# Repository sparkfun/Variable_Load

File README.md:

SparkFun Variable Load
==========================================

[*Variable Load (KIT-14449)*](https://www.sparkfun.com/products/14449)

The Variable Load is a digitally controllable load for testing power supplies.
It can test up to 30V at 4A, with a limit of 15W.

Repository Contents
-------------------
* **/Hardware** - All Eagle design files (.brd, .sch)
* **/Firmware** - Firmware files for this project.
* **/Production** - Test bed files and production panel files

Documentation
--------------

* **[Hookup Guide - Revised](https://learn.sparkfun.com/tutorials/variable-load-hookup-guide---revised)** - Latest basic hookup guide for the Variable Load.
* ***[Hookup Guide (RETIRED)](https://learn.sparkfun.com/tutorials/variable-load-hookup-guide)** - Basic hookup guide for the Variable Load for boards purchased purchased prior to 24 May 2018.*

License Information
-------------------

This product is _**open source**_! 

Please review the LICENSE.md file for license information. 

If you have any questions or concerns on licensing, please contact techsupport@sparkfun.com.

Distributed as-is; no warranty is given.

- Your friends at SparkFun.

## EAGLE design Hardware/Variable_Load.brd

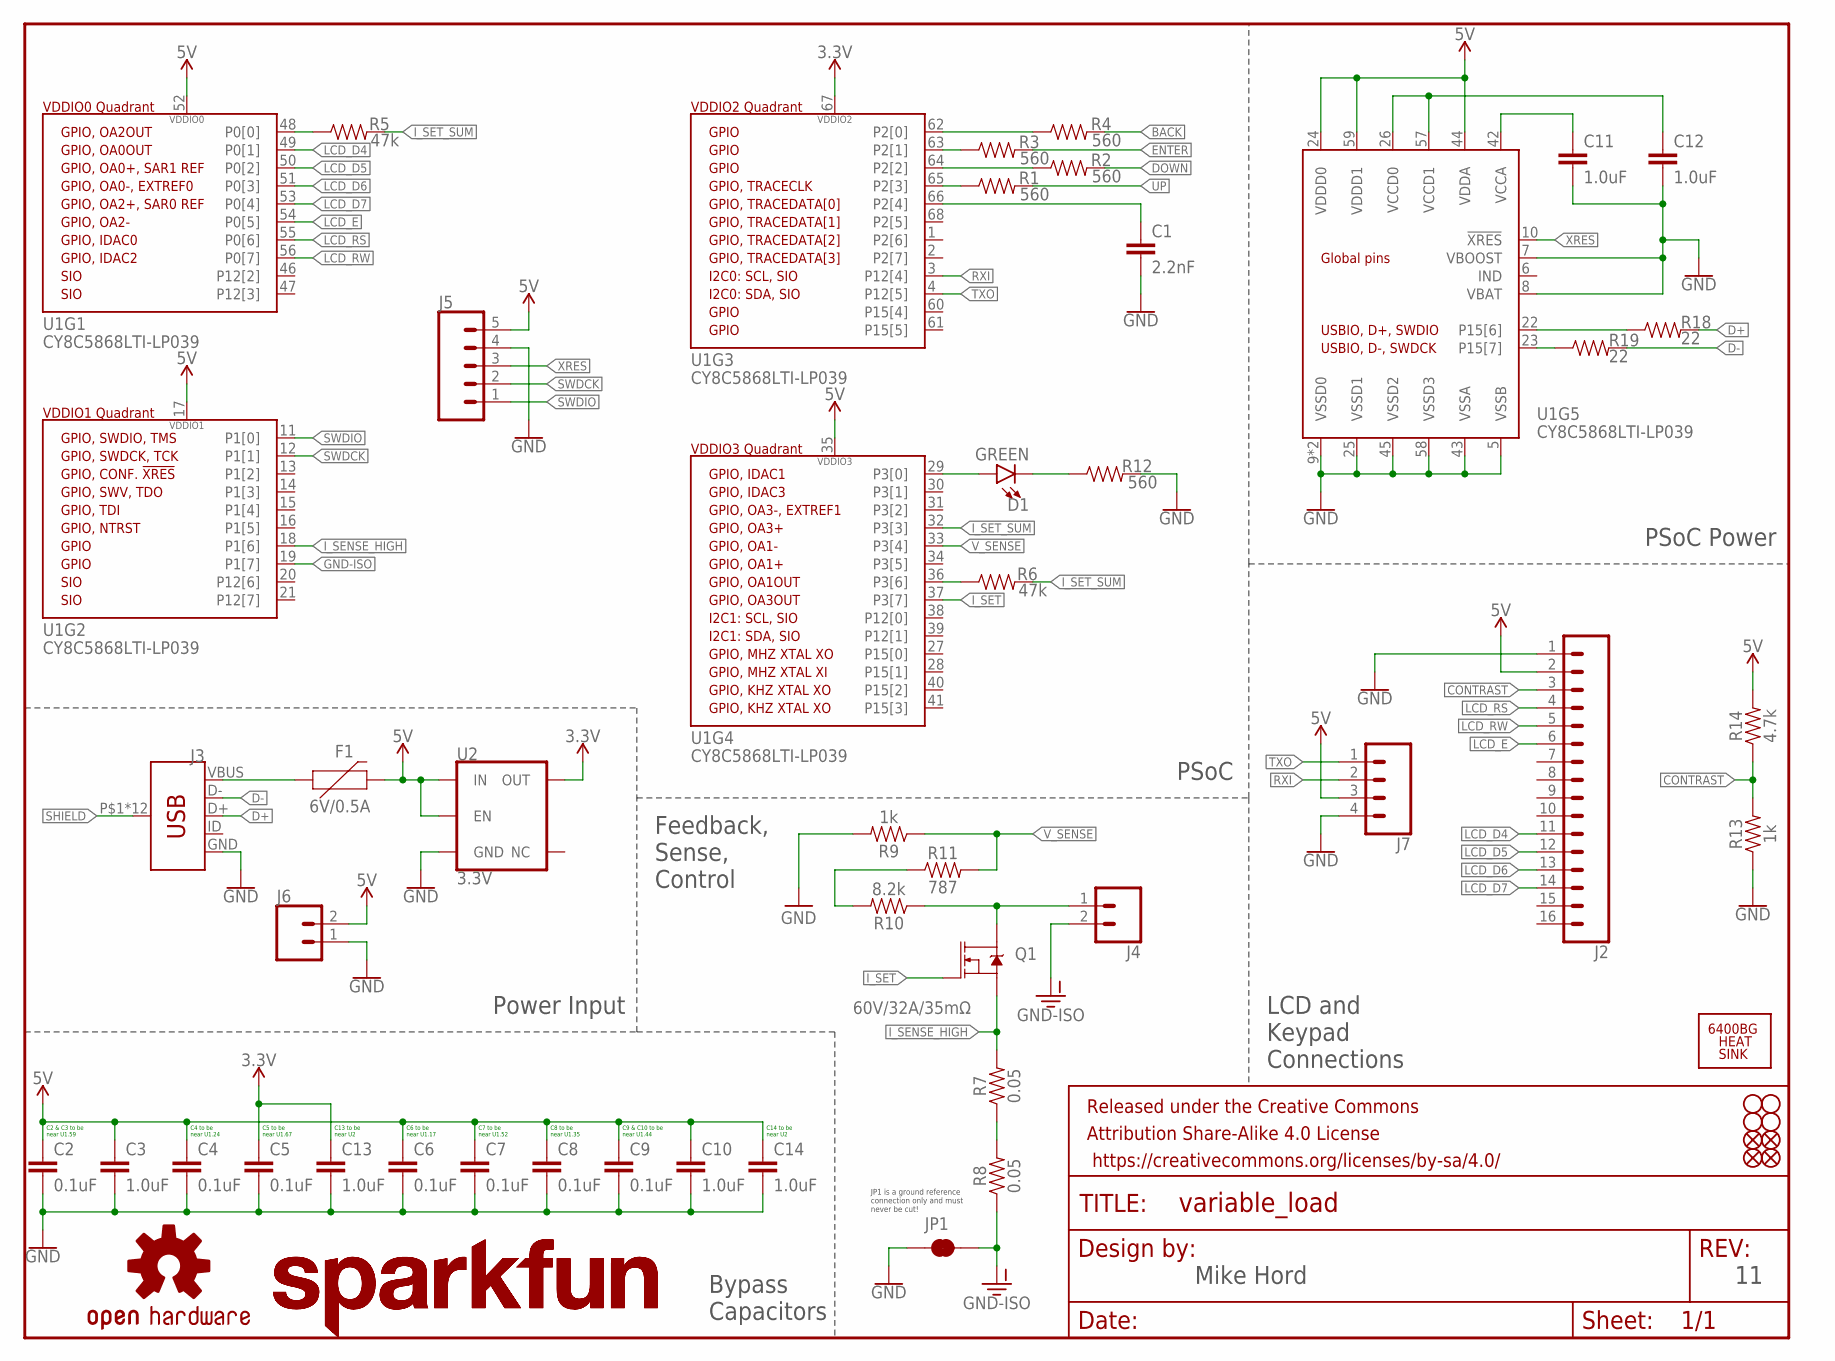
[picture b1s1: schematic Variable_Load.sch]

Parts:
C1: 2.2nF; 0603
C2, C4, C5, C6, C7, C8, C9: 0.1uF; 0402
C3, C10, C11, C12, C13, C14: 1.0uF; 0402
D1: GREEN; LED-1206-BOTTOM
F1: 6V/0.5A; 1206
FD1, FD2, FD3, FD4: FIDUCIAL1X2; FIDUCIAL-1X2
FRAME1: FRAME-LETTER; CREATIVE_COMMONS
H1: 6400BG_HEATSINK
H2, H3, H4, H5: STAND-OFF
J2: CONN_16; 1X16
J3: AMP FCI 10103594-0001LF; USB-MICROB-PTH
J4: CONN_023.5MM_LOCK; SCREWTERMINAL-3.5MM-2_LOCK
J5: CONN_05; 1X05
J6: CONN_02; 1X02
J7: CONN_04; 1X04
JP1: JUMPER-SMT_2_NC_TRACE_NO-SILK; SMT-JUMPER_2_NC_TRACE_NO-SILK
LOGO1: OSHW-LOGOM; OSHW-LOGO-M
LOGO2, LOGO3: SFE_LOGO_NAME.3_INCH; SFE_LOGO_NAME_.3
Q1: 60V/32A/35mΩ; TO220V
R1, R2, R3, R4, R12: 560; 0402
R5, R6: 47k; 0603
R7, R8: 0.05; 2512
R9, R13: 1k; 0603
R10: 8.2k; 0603
R11: 787; 0603
R14: 4.7k; 0603
R18, R19: 22; 0402-RES
U1: CY8C5868LTI-LP039; QFN-68
U2: 3.3V; SOT23-5

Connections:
3.3V: C5.1, C13.1, U1.67 (VDDIO2), U2.5 (OUT)
5V: C2.1, C3.1, C4.1, C6.1, C7.1, C8.1, C9.1, C10.1, C14.1, F1.2, J2.2, J5.5, J6.2, J7.3, R14.2, U1.17 (VDDIO1), U1.24 (VDDD0), U1.35 (VDDIO3), U1.44 (VDDA), U1.52 (VDDIO0), U1.59 (VDDD1), U2.1 (IN), U2.3 (EN)
BACK: R4.2
CONTRAST: J2.3, R13.2, R14.1
D+: J3.D+, R18.2
D-: J3.D-, R19.2
DOWN: R2.2
ENTER: R3.2
GND: C1.2, C2.2, C3.2, C4.2, C5.2, C6.2, C7.2, C8.2, C9.2, C10.2, C11.2, C12.2, C13.2, C14.2, J2.1, J3.GND, J5.4, J6.1, J7.4, JP1.1, R9.2, R12.2, R13.1, U1.5 (VSSB), U1.7 (VBOOST), U1.8 (VBAT), U1.9 (VSSD0), U1.25 (VSSD1), U1.43 (VSSA), U1.45 (VSSD2), U1.58 (VSSD3), U1.69 (VSSD0), U2.2 (GND)
GND-ISO: J4.2, JP1.2, R8.P$1 (1), U1.19 (P1[7])
I_SENSE_HIGH: Q1.3 (S), R7.P$2 (2), U1.18 (P1[6])
I_SET: Q1.1 (G), U1.37 (P3[7])
I_SET_SUM: R5.2, R6.2, U1.32 (P3[3])
LCD_D4: J2.11, U1.49 (P0[1])
LCD_D5: J2.12, U1.50 (P0[2])
LCD_D6: J2.13, U1.51 (P0[3])
LCD_D7: J2.14, U1.53 (P0[4])
LCD_E: J2.6, U1.54 (P0[5])
LCD_RS: J2.4, U1.55 (P0[6])
LCD_RW: J2.5, U1.56 (P0[7])
unnamed: R1.1, U1.65 (P2[3])
unnamed: R2.1, U1.64 (P2[2])
unnamed: R3.1, U1.63 (P2[1])
unnamed: R4.1, U1.62 (P2[0])
unnamed: C1.1, U1.66 (P2[4])
unnamed: C12.1, U1.26 (VCCD0), U1.57 (VCCD1)
unnamed: C11.1, U1.42 (VCCA)
unnamed: R18.1, U1.22 (P15[6])
unnamed: R19.1, U1.23 (P15[7])
unnamed: R5.1, U1.48 (P0[0])
unnamed: R6.1, U1.36 (P3[6])
unnamed: D1.A, U1.29 (P3[0])
unnamed: D1.C, R12.1
unnamed: F1.1, J3.VBUS
unnamed: J4.1, Q1.2 (D), R10.1
unnamed: R10.2, R11.1
unnamed: R7.P$1 (1), R8.P$2 (2)
RXI: J7.2, U1.3 (P12[4])
SHIELD: J3.P$1 (SHIELD), J3.P$2 (SHIELD), J3.P$3 (SHIELD), J3.P$4 (SHIELD), J3.P$6 (SHIELD), J3.P$8 (SHIELD), J3.P$10 (SHIELD), J3.P$12 (SHIELD), J3.SHEILD2 (SHIELD), J3.SHIELD, J3.SHIELD3 (SHIELD), J3.SHIELD4 (SHIELD)
SWDCK: J5.2, U1.12 (P1[1])
SWDIO: J5.1, U1.11 (P1[0])
TXO: J7.1, U1.4 (P12[5])
UP: R1.2
V_SENSE: R9.1, R11.2, U1.33 (P3[4])
XRES: J5.3, U1.10 (!XRES)

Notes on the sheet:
C2 & C3 to be near U1.59
C4 to be near U1.24
C5 to be near U1.67
C6 to be near U1.17
C7 to be near U1.52
C8 to be near U1.35
C9 & C10 to be near U1.44
C13 to be near U2
C14 to be near U2
Feedback, Sense, Control
Power Input
LCD and Keypad Connections
PSoC Power
PSoC
Bypass Capacitors
Mike Hord
JP1 is a ground reference connection only and must never be cut!

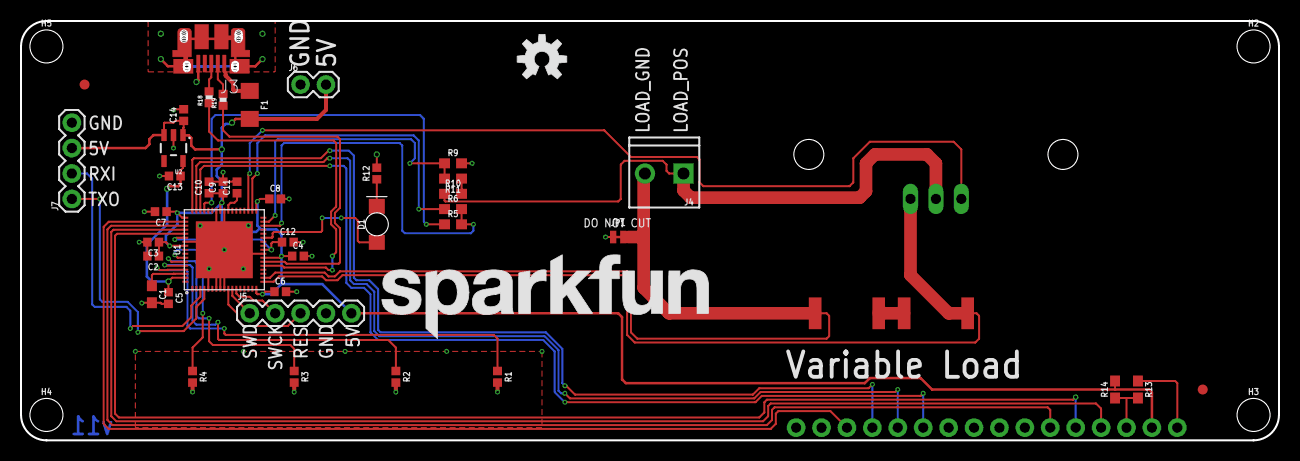
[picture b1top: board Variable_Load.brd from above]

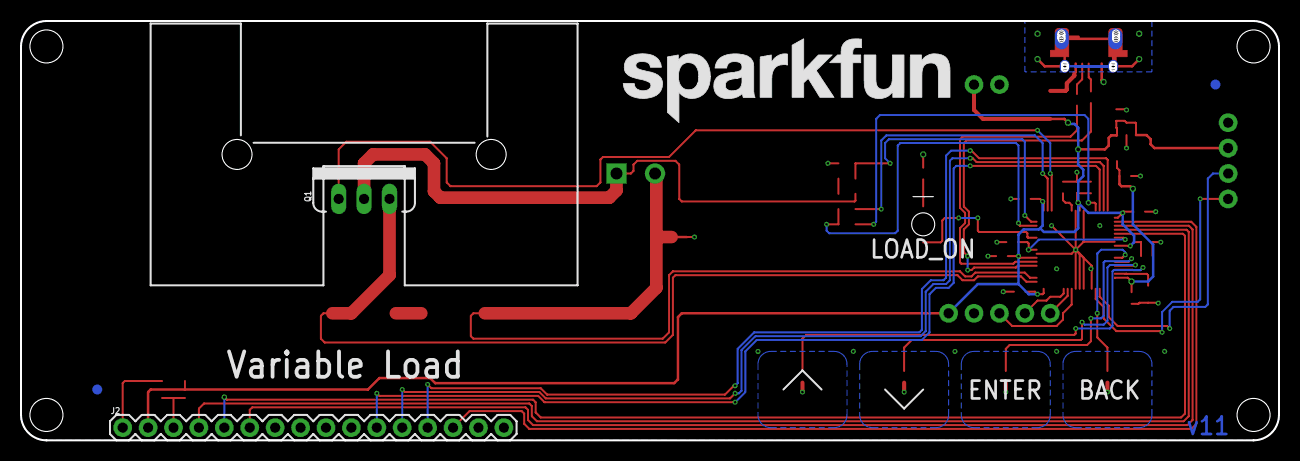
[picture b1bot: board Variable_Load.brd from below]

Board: 2 copper layers, 125.7 x 41.9 mm, 55 parts (6 on the bottom side), 41 nets.

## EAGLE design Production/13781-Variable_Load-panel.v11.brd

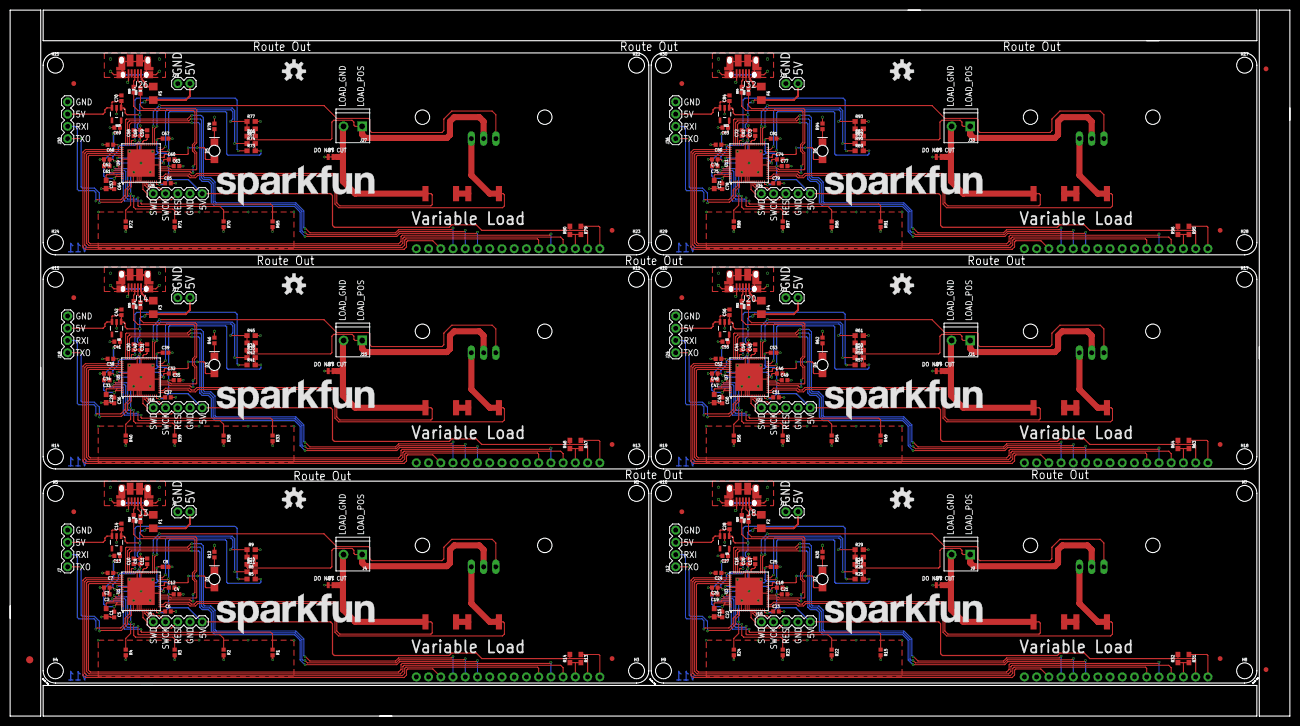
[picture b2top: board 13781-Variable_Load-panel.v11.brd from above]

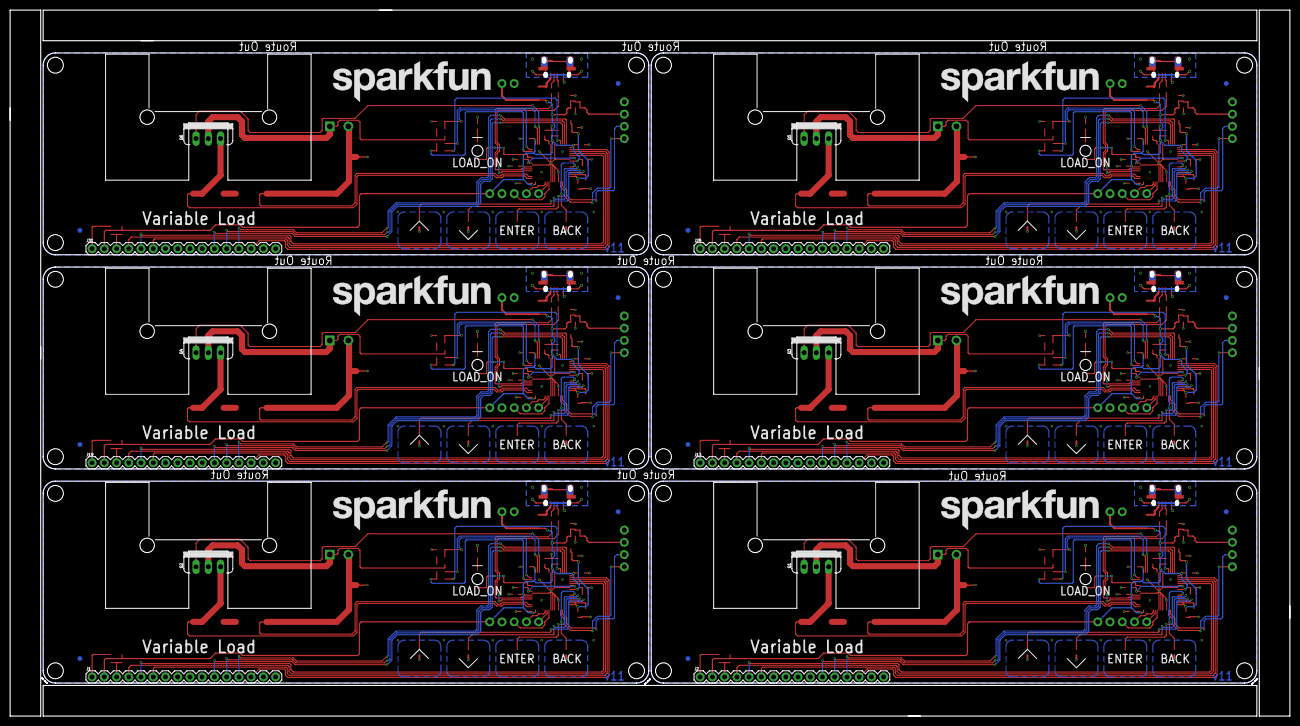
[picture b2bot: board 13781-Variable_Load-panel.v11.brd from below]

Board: 2 copper layers, 265.7 x 146.6 mm, 327 parts (36 on the bottom side), 246 nets.

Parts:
C1, C15, C29, C43, C57, C71: 2.2nF; 0603
C2, C4, C5, C6, C7, C8, C9, C19, C21, C22, C23, C24, C25, C26, C33, C35, C36, C37, C38, C39, C40, C47, C49, C50, C51, C52, C53, C54, C61, C63, C64, C65, C66, C67, C68, C75, C77, C78, C79, C80, C81, C82: 0.1uF; 0402
C3, C10, C11, C12, C13, C14, C16, C17, C18, C20, C27, C28, C30, C31, C32, C34, C41, C42, C44, C45, C46, C48, C55, C56, C58, C59, C60, C62, C69, C70, C72, C73, C74, C76, C83, C84: 1.0uF; 0402
D1, D2, D3, D4, D5, D6: GREEN; LED-1206-BOTTOM
E$1: FIDUCIAL-1.5X3
E$7, E$8: FIDUCIAL-1X2
F1, F2, F3, F4, F5, F6: 6V/0.5A; 1206
FD1, FD2, FD3, FD4, FD5, FD6, FD7, FD8, FD9, FD10, FD11, FD12, FD13, FD14, FD15, FD16, FD17, FD18, FD19, FD20, FD21, FD22, FD23, FD24: FIDUCIAL1X2; FIDUCIAL-1X2
H1, H6, H11, H16, H21, H26: 6400BG_HEATSINK
H2, H3, H4, H5, H7, H8, H9, H10, H12, H13, H14, H15, H17, H18, H19, H20, H22, H23, H24, H25, H27, H28, H29, H30: STAND-OFF
J1, J2, J13, J19, J25, J31: 1X16
J3, J8, J14, J20, J26, J32: AMP FCI 10103594-0001LF; USB-MICROB-PTH
J4, J9, J15, J21, J27, J33: SCREWTERMINAL-3.5MM-2_LOCK
J5, J10, J16, J22, J28, J34: 1X05
J6, J11, J17, J23, J29, J35: 1X02
J7, J12, J18, J24, J30, J36: 1X04
JP1, JP2, JP3, JP4, JP5, JP6: JUMPER-SMT_2_NC_TRACE_NO-SILK; SMT-JUMPER_2_NC_TRACE_NO-SILK
LOGO1, LOGO4, LOGO7, LOGO10, LOGO13, LOGO16: OSHW-LOGOM; OSHW-LOGO-M
LOGO2, LOGO3, LOGO5, LOGO6, LOGO8, LOGO9, LOGO11, LOGO12, LOGO14, LOGO15, LOGO17, LOGO18: SFE_LOGO_NAME.3_INCH; SFE_LOGO_NAME_.3
Q1, Q2, Q3, Q4, Q5, Q6: 60V/32A/35mΩ; TO220V
R1, R2, R3, R4, R12, R15, R22, R23, R24, R30, R33, R38, R39, R40, R46, R49, R54, R55, R56, R62, R65, R70, R71, R72, R78, R81, R86, R87, R88, R94: 560; 0402
R5, R6, R25, R26, R41, R42, R57, R58, R73, R74, R89, R90: 47k; 0603
R7, R8, R27, R28, R43, R44, R59, R60, R75, R76, R91, R92: 0.05; 2512
R9, R13, R29, R31, R45, R47, R61, R63, R77, R79, R93, R95: 1k; 0603
R10, R16, R34, R50, R66, R82: 8.2k; 0603
R11, R17, R35, R51, R67, R83: 787; 0603
R14, R32, R48, R64, R80, R96: 4.7k; 0603
R18, R19, R20, R21, R36, R37, R52, R53, R68, R69, R84, R85: 22; 0402-RES
U1, U3, U5, U7, U9, U11: CY8C5868LTI-LP039; QFN-68
U2, U4, U6, U8, U10, U12: 3.3V; SOT23-5

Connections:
3.3V: C5.1, C13.1, U1.67, U2.5
3.3V1: C22.1, C27.1, U3.67, U4.5
3.3V2: C36.1, C41.1, U5.67, U6.5
3.3V3: C50.1, C55.1, U7.67, U8.5
3.3V4: C64.1, C69.1, U9.67, U10.5
3.3V5: C78.1, C83.1, U11.67, U12.5
5V: C2.1, C3.1, C4.1, C6.1, C7.1, C8.1, C9.1, C10.1, C14.1, F1.2, J2.2, J5.5, J6.2, J7.3, R14.2, U1.17, U1.24, U1.35, U1.44, U1.52, U1.59, U2.1, U2.3
5V1: C16.1, C19.1, C20.1, C21.1, C23.1, C24.1, C25.1, C26.1, C28.1, F2.2, J1.2, J10.5, J11.2, J12.3, R32.2, U3.17, U3.24, U3.35, U3.44, U3.52, U3.59, U4.1, U4.3
5V2: C30.1, C33.1, C34.1, C35.1, C37.1, C38.1, C39.1, C40.1, C42.1, F3.2, J13.2, J16.5, J17.2, J18.3, R48.2, U5.17, U5.24, U5.35, U5.44, U5.52, U5.59, U6.1, U6.3
5V3: C44.1, C47.1, C48.1, C49.1, C51.1, C52.1, C53.1, C54.1, C56.1, F4.2, J19.2, J22.5, J23.2, J24.3, R64.2, U7.17, U7.24, U7.35, U7.44, U7.52, U7.59, U8.1, U8.3
5V4: C58.1, C61.1, C62.1, C63.1, C65.1, C66.1, C67.1, C68.1, C70.1, F5.2, J25.2, J28.5, J29.2, J30.3, R80.2, U9.17, U9.24, U9.35, U9.44, U9.52, U9.59, U10.1, U10.3
5V5: C72.1, C75.1, C76.1, C77.1, C79.1, C80.1, C81.1, C82.1, C84.1, F6.2, J31.2, J34.5, J35.2, J36.3, R96.2, U11.17, U11.24, U11.35, U11.44, U11.52, U11.59, U12.1, U12.3
CONTRAST: J2.3, R13.2, R14.1
CONTRAST1: J1.3, R31.2, R32.1
CONTRAST2: J13.3, R47.2, R48.1
CONTRAST3: J19.3, R63.2, R64.1
CONTRAST4: J25.3, R79.2, R80.1
CONTRAST5: J31.3, R95.2, R96.1
D+: J3.D+, R18.2
D+1: J8.D+, R20.2
D+2: J14.D+, R36.2
D+3: J20.D+, R52.2
D+4: J26.D+, R68.2
D+5: J32.D+, R84.2
D-: J3.D-, R19.2
D-1: J8.D-, R21.2
D-2: J14.D-, R37.2
D-3: J20.D-, R53.2
D-4: J26.D-, R69.2
D-5: J32.D-, R85.2
GND: C1.2, C2.2, C3.2, C4.2, C5.2, C6.2, C7.2, C8.2, C9.2, C10.2, C11.2, C12.2, C13.2, C14.2, J2.1, J3.GND, J5.4, J6.1, J7.4, JP1.1, R9.2, R12.2, R13.1, U1.5, U1.7, U1.8, U1.9, U1.25, U1.43, U1.45, U1.58, U1.69, U2.2
GND1: C15.2, C16.2, C17.2, C18.2, C19.2, C20.2, C21.2, C22.2, C23.2, C24.2, C25.2, C26.2, C27.2, C28.2, J1.1, J8.GND, J10.4, J11.1, J12.4, JP2.1, R29.2, R30.2, R31.1, U3.5, U3.7, U3.8, U3.9, U3.25, U3.43, U3.45, U3.58, U3.69, U4.2
GND2: C29.2, C30.2, C31.2, C32.2, C33.2, C34.2, C35.2, C36.2, C37.2, C38.2, C39.2, C40.2, C41.2, C42.2, J13.1, J14.GND, J16.4, J17.1, J18.4, JP3.1, R45.2, R46.2, R47.1, U5.5, U5.7, U5.8, U5.9, U5.25, U5.43, U5.45, U5.58, U5.69, U6.2
GND3: C43.2, C44.2, C45.2, C46.2, C47.2, C48.2, C49.2, C50.2, C51.2, C52.2, C53.2, C54.2, C55.2, C56.2, J19.1, J20.GND, J22.4, J23.1, J24.4, JP4.1, R61.2, R62.2, R63.1, U7.5, U7.7, U7.8, U7.9, U7.25, U7.43, U7.45, U7.58, U7.69, U8.2
GND4: C57.2, C58.2, C59.2, C60.2, C61.2, C62.2, C63.2, C64.2, C65.2, C66.2, C67.2, C68.2, C69.2, C70.2, J25.1, J26.GND, J28.4, J29.1, J30.4, JP5.1, R77.2, R78.2, R79.1, U9.5, U9.7, U9.8, U9.9, U9.25, U9.43, U9.45, U9.58, U9.69, U10.2
GND5: C71.2, C72.2, C73.2, C74.2, C75.2, C76.2, C77.2, C78.2, C79.2, C80.2, C81.2, C82.2, C83.2, C84.2, J31.1, J32.GND, J34.4, J35.1, J36.4, JP6.1, R93.2, R94.2, R95.1, U11.5, U11.7, U11.8, U11.9, U11.25, U11.43, U11.45, U11.58, U11.69, U12.2
GND-ISO: J4.2, JP1.2, R8.P$1, U1.19
GND-ISO1: J9.2, JP2.2, R28.P$1, U3.19
GND-ISO2: J15.2, JP3.2, R44.P$1, U5.19
GND-ISO3: J21.2, JP4.2, R60.P$1, U7.19
GND-ISO4: J27.2, JP5.2, R76.P$1, U9.19
GND-ISO5: J33.2, JP6.2, R92.P$1, U11.19
I_SENSE_HIGH: Q1.3, R7.P$2, U1.18
I_SENSE_HIGH1: Q2.3, R27.P$2, U3.18
I_SENSE_HIGH2: Q3.3, R43.P$2, U5.18
I_SENSE_HIGH3: Q4.3, R59.P$2, U7.18
I_SENSE_HIGH4: Q5.3, R75.P$2, U9.18
I_SENSE_HIGH5: Q6.3, R91.P$2, U11.18
I_SET: Q1.1, U1.37
I_SET1: Q2.1, U3.37
I_SET2: Q3.1, U5.37
I_SET3: Q4.1, U7.37
I_SET4: Q5.1, U9.37
I_SET5: Q6.1, U11.37
I_SET_SUM: R5.2, R6.2, U1.32
I_SET_SUM1: R25.2, R26.2, U3.32
I_SET_SUM2: R41.2, R42.2, U5.32
I_SET_SUM3: R57.2, R58.2, U7.32
I_SET_SUM4: R73.2, R74.2, U9.32
I_SET_SUM5: R89.2, R90.2, U11.32
LCD_D1: J1.11, U3.49
LCD_D2: J1.12, U3.50
LCD_D3: J1.13, U3.51
LCD_D4: J2.11, U1.49
LCD_D5: J2.12, U1.50
LCD_D6: J2.13, U1.51
LCD_D7: J2.14, U1.53
LCD_D8: J1.14, U3.53
LCD_D9: J13.11, U5.49
LCD_D10: J13.12, U5.50
LCD_D11: J13.13, U5.51
LCD_D12: J13.14, U5.53
LCD_D13: J19.11, U7.49
LCD_D14: J19.12, U7.50
LCD_D15: J19.13, U7.51
LCD_D16: J19.14, U7.53
LCD_D17: J25.11, U9.49
LCD_D18: J25.12, U9.50
LCD_D19: J25.13, U9.51
LCD_D20: J25.14, U9.53
LCD_D21: J31.11, U11.49
LCD_D22: J31.12, U11.50
LCD_D23: J31.13, U11.51
LCD_D24: J31.14, U11.53
LCD_E: J2.6, U1.54
LCD_E1: J1.6, U3.54
LCD_E2: J13.6, U5.54
LCD_E3: J19.6, U7.54
LCD_E4: J25.6, U9.54
LCD_E5: J31.6, U11.54
LCD_RS: J2.4, U1.55
LCD_RS1: J1.4, U3.55
LCD_RS2: J13.4, U5.55
LCD_RS3: J19.4, U7.55
LCD_RS4: J25.4, U9.55
LCD_RS5: J31.4, U11.55
LCD_RW: J2.5, U1.56
LCD_RW1: J1.5, U3.56
LCD_RW2: J13.5, U5.56
LCD_RW3: J19.5, U7.56
LCD_RW4: J25.5, U9.56
LCD_RW5: J31.5, U11.56
unnamed: R1.1, U1.65
unnamed: R2.1, U1.64
unnamed: R3.1, U1.63
unnamed: R4.1, U1.62
unnamed: C1.1, U1.66
unnamed: C12.1, U1.26, U1.57
unnamed: C11.1, U1.42
unnamed: R18.1, U1.22
unnamed: R19.1, U1.23
unnamed: R5.1, U1.48
unnamed: R6.1, U1.36
unnamed: D1.A, U1.29
unnamed: D1.C, R12.1
unnamed: F1.1, J3.VBUS
unnamed: J4.1, Q1.2, R10.1
unnamed: R10.2, R11.1
unnamed: C15.1, U3.66
unnamed: R7.P$1, R8.P$2
unnamed: R25.1, U3.48
unnamed: C18.1, U3.26, U3.57
unnamed: C17.1, U3.42
unnamed: R20.1, U3.22
unnamed: R21.1, U3.23
unnamed: F2.1, J8.VBUS
unnamed: J9.1, Q2.2, R16.1
unnamed: R16.2, R17.1
unnamed: R27.P$1, R28.P$2
unnamed: R15.1, U3.65
unnamed: R22.1, U3.64
unnamed: R23.1, U3.63
unnamed: R24.1, U3.62
unnamed: R26.1, U3.36
unnamed: D2.A, U3.29
unnamed: D2.C, R30.1
unnamed: C29.1, U5.66
unnamed: R41.1, U5.48
unnamed: C32.1, U5.26, U5.57
unnamed: C31.1, U5.42
unnamed: R36.1, U5.22
unnamed: R37.1, U5.23
unnamed: F3.1, J14.VBUS
unnamed: J15.1, Q3.2, R34.1
unnamed: R34.2, R35.1
unnamed: R43.P$1, R44.P$2
unnamed: R33.1, U5.65
unnamed: R38.1, U5.64
unnamed: R39.1, U5.63
unnamed: R40.1, U5.62
unnamed: R42.1, U5.36
unnamed: D3.A, U5.29
unnamed: D3.C, R46.1
unnamed: C43.1, U7.66
unnamed: R57.1, U7.48
unnamed: C46.1, U7.26, U7.57
unnamed: C45.1, U7.42
unnamed: R52.1, U7.22
unnamed: R53.1, U7.23
unnamed: F4.1, J20.VBUS
unnamed: J21.1, Q4.2, R50.1
unnamed: R50.2, R51.1
unnamed: R59.P$1, R60.P$2
unnamed: R49.1, U7.65
unnamed: R54.1, U7.64
unnamed: R55.1, U7.63
unnamed: R56.1, U7.62
unnamed: R58.1, U7.36
unnamed: D4.A, U7.29
unnamed: D4.C, R62.1
unnamed: C57.1, U9.66
unnamed: R73.1, U9.48
unnamed: C60.1, U9.26, U9.57
unnamed: C59.1, U9.42
unnamed: R68.1, U9.22
unnamed: R69.1, U9.23
unnamed: F5.1, J26.VBUS
unnamed: J27.1, Q5.2, R66.1
unnamed: R66.2, R67.1
unnamed: R75.P$1, R76.P$2
unnamed: R65.1, U9.65
unnamed: R70.1, U9.64
unnamed: R71.1, U9.63
unnamed: R72.1, U9.62
unnamed: R74.1, U9.36
unnamed: D5.A, U9.29
unnamed: D5.C, R78.1
unnamed: C71.1, U11.66
unnamed: R89.1, U11.48
unnamed: C74.1, U11.26, U11.57
unnamed: C73.1, U11.42
unnamed: R84.1, U11.22
unnamed: R85.1, U11.23
unnamed: F6.1, J32.VBUS
unnamed: J33.1, Q6.2, R82.1
unnamed: R82.2, R83.1
unnamed: R91.P$1, R92.P$2
unnamed: R81.1, U11.65
unnamed: R86.1, U11.64
unnamed: R87.1, U11.63
unnamed: R88.1, U11.62
unnamed: R90.1, U11.36
unnamed: D6.A, U11.29
unnamed: D6.C, R94.1
RXI: J7.2, U1.3
RXI1: J12.2, U3.3
RXI2: J18.2, U5.3
RXI3: J24.2, U7.3
RXI4: J30.2, U9.3
RXI5: J36.2, U11.3
SHIELD: J3.P$1, J3.P$2, J3.P$3, J3.P$4, J3.P$6, J3.P$8, J3.P$10, J3.P$12, J3.SHEILD2, J3.SHIELD, J3.SHIELD3, J3.SHIELD4
SHIELD1: J8.P$1, J8.P$2, J8.P$3, J8.P$4, J8.P$6, J8.P$8, J8.P$10, J8.P$12, J8.SHEILD2, J8.SHIELD, J8.SHIELD3, J8.SHIELD4
SHIELD2: J14.P$1, J14.P$2, J14.P$3, J14.P$4, J14.P$6, J14.P$8, J14.P$10, J14.P$12, J14.SHEILD2, J14.SHIELD, J14.SHIELD3, J14.SHIELD4
SHIELD3: J20.P$1, J20.P$2, J20.P$3, J20.P$4, J20.P$6, J20.P$8, J20.P$10, J20.P$12, J20.SHEILD2, J20.SHIELD, J20.SHIELD3, J20.SHIELD4
SHIELD4: J26.P$1, J26.P$2, J26.P$3, J26.P$4, J26.P$6, J26.P$8, J26.P$10, J26.P$12, J26.SHEILD2, J26.SHIELD, J26.SHIELD3, J26.SHIELD4
SHIELD5: J32.P$1, J32.P$2, J32.P$3, J32.P$4, J32.P$6, J32.P$8, J32.P$10, J32.P$12, J32.SHEILD2, J32.SHIELD, J32.SHIELD3, J32.SHIELD4
SWDCK: J5.2, U1.12
SWDCK1: J10.2, U3.12
SWDCK2: J16.2, U5.12
SWDCK3: J22.2, U7.12
SWDCK4: J28.2, U9.12
SWDCK5: J34.2, U11.12
SWDIO: J5.1, U1.11
SWDIO1: J10.1, U3.11
SWDIO2: J16.1, U5.11
SWDIO3: J22.1, U7.11
SWDIO4: J28.1, U9.11
SWDIO5: J34.1, U11.11
TXO: J7.1, U1.4
TXO1: J12.1, U3.4
TXO2: J18.1, U5.4
TXO3: J24.1, U7.4
TXO4: J30.1, U9.4
TXO5: J36.1, U11.4
V_SENSE: R9.1, R11.2, U1.33
V_SENSE1: R17.2, R29.1, U3.33
V_SENSE2: R35.2, R45.1, U5.33
V_SENSE3: R51.2, R61.1, U7.33
V_SENSE4: R67.2, R77.1, U9.33
V_SENSE5: R83.2, R93.1, U11.33
XRES: J5.3, U1.10
XRES1: J10.3, U3.10
XRES2: J16.3, U5.10
XRES3: J22.3, U7.10
XRES4: J28.3, U9.10
XRES5: J34.3, U11.10

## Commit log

2017-08-15 Removed header for CT keypad
2017-08-17 Post review, pre attempting to get to two layers
2017-08-17 Made into a two-layer design
2017-08-23 Corrections from QC double check
2017-09-01 Replace USB jack with newer, bossed design
2017-10-02 Add firmware, latest changes to HW
2017-10-03 Changes from design review
2017-10-03 Change ON label to LOAD_ON
2017-10-03 panel
2017-11-14 Firmware changes after red board
2017-11-20 Changes for 2nd proto round
2017-11-28 Added resistor divider for contrast
2017-11-28 Change font to vector on schematic
2018-02-19 Fix issue with firmware, add readme and license files
2018-02-22 Add readme and license
2018-03-04 Change to use integer math for PID. Change to use feedforward in PID. Change to trigger ADC with hardware clock and do PID calcualtion in ISR. Change to average voltage ADC readings to reduce noise.
2018-03-04 Improve precision of current measurement. Add ability to set vMin and enable/disable load from terminal.
2018-03-05 Improve precision of current measurement. Add ability to set vMin and enable/disable load from terminal. Use internal reference for source voltage ADC (rather than 1/2 the supply voltage). This make 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
2018-03-05 Change to averge current reading. Change to use internal reference for voltage measuremnt rather than supply/2 to improve accuracy. This reduces the range to about 20V with the 10:1 divider. Ideally 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
2018-03-05 Fixed current measurment averaging. There are a number of subtleties with regard to DMA and the DelSigADC. Fortunately there is a Cypress app note that describes how to make it work. Added mAhour com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
2018-03-13 Add INF File
2018-05-22 Changes implemented
2018-05-23 Add bootloader files
2018-05-25 Chg for QC, remove Digital_Load files
2020-11-15 Added Constant-Power draw. Increased PID frequency and changed PID from F-I control to real PI control. Power limit changed to 50W,

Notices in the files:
parts and their libraries:
SparkFun-Capacitors: Licensing: Creative Commons ShareAlike 4.0 International - https://creativecommons.org/licenses/by-sa/4.0
SparkFun-Aesthetics: Released under the Creative Commons Attribution Share-Alike 4.0 License
SparkFun-Aesthetics: https://creativecommons.org/licenses/by-sa/4.0
